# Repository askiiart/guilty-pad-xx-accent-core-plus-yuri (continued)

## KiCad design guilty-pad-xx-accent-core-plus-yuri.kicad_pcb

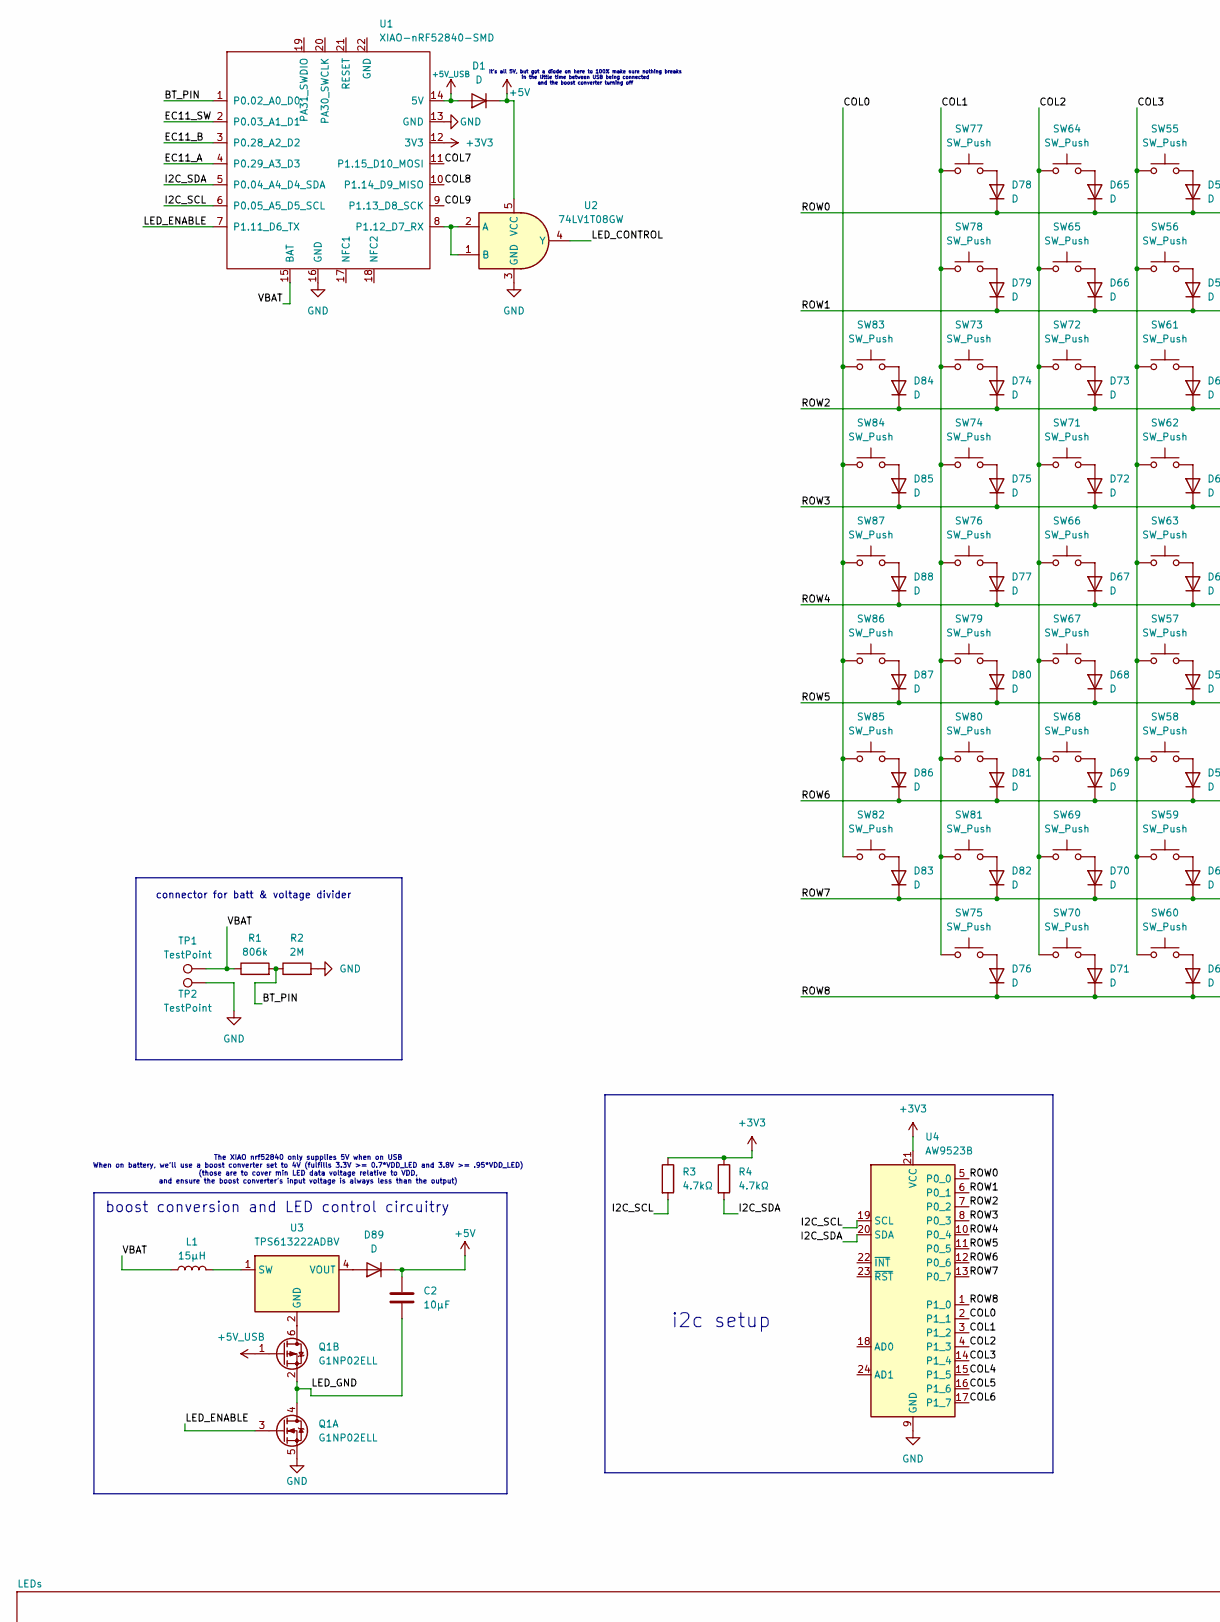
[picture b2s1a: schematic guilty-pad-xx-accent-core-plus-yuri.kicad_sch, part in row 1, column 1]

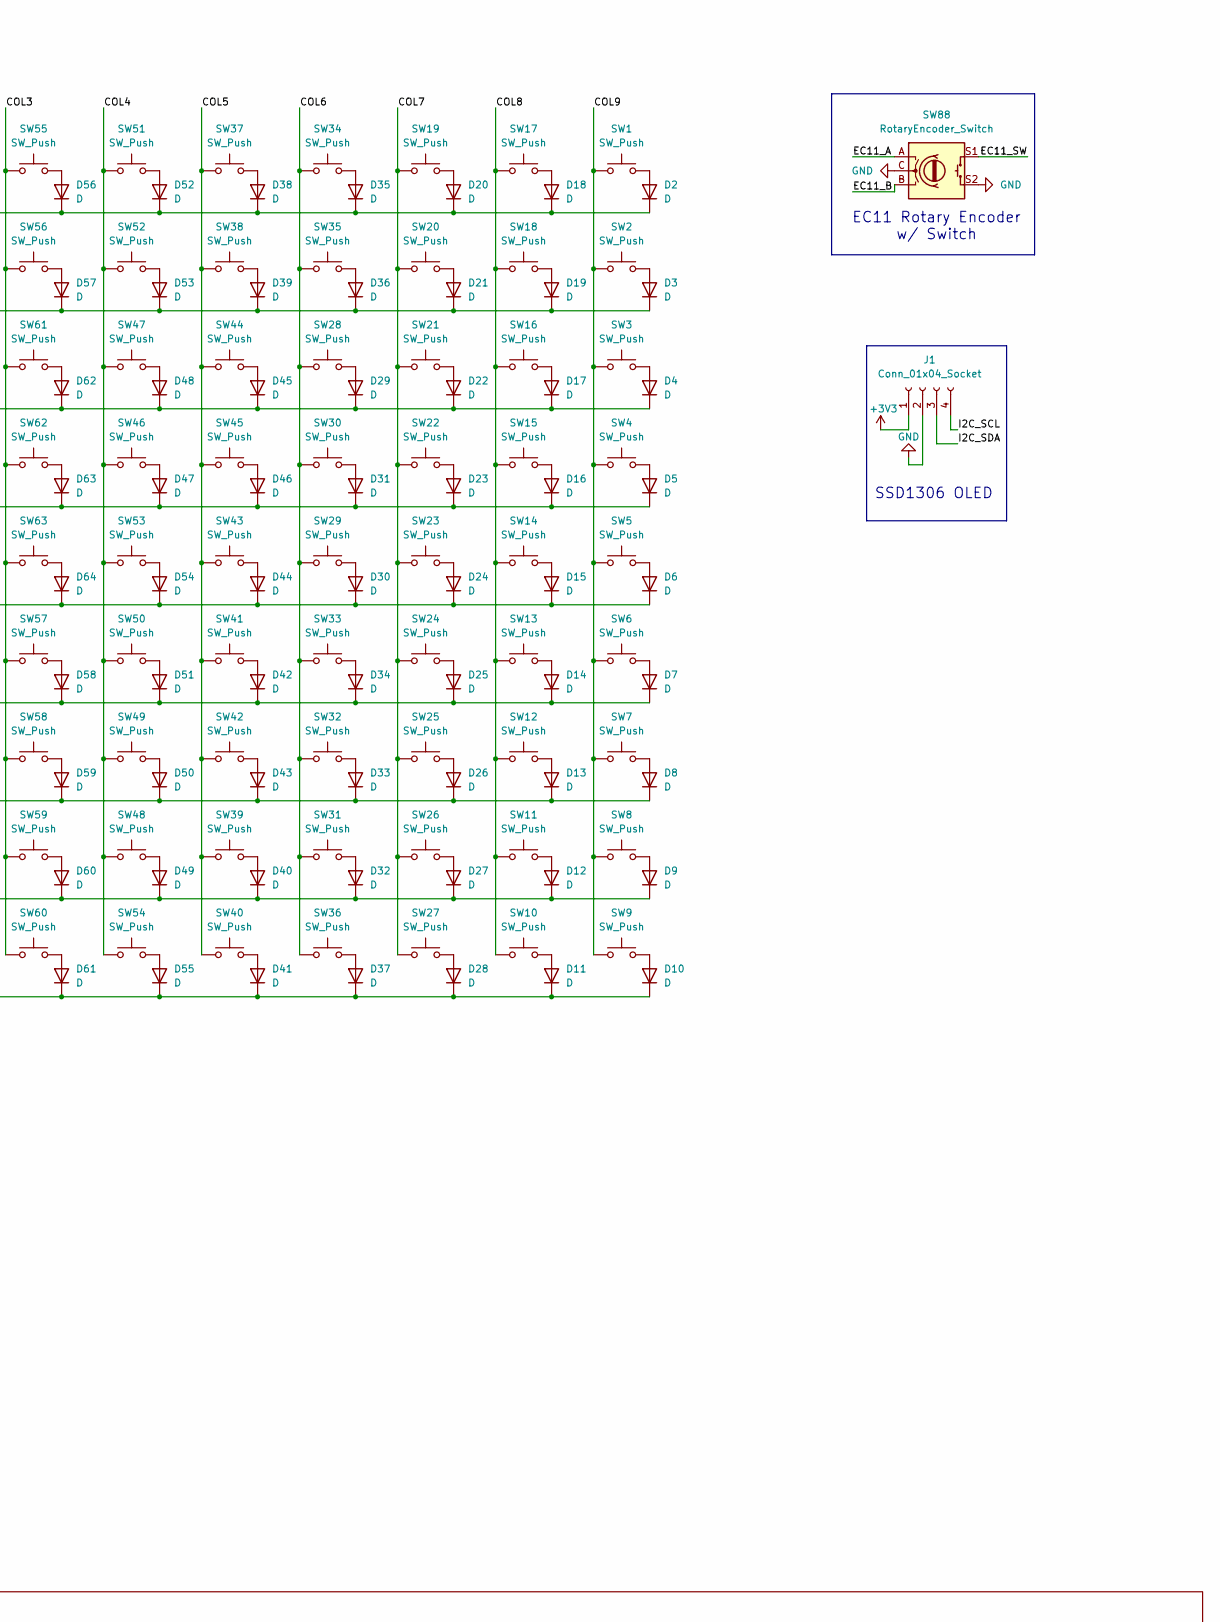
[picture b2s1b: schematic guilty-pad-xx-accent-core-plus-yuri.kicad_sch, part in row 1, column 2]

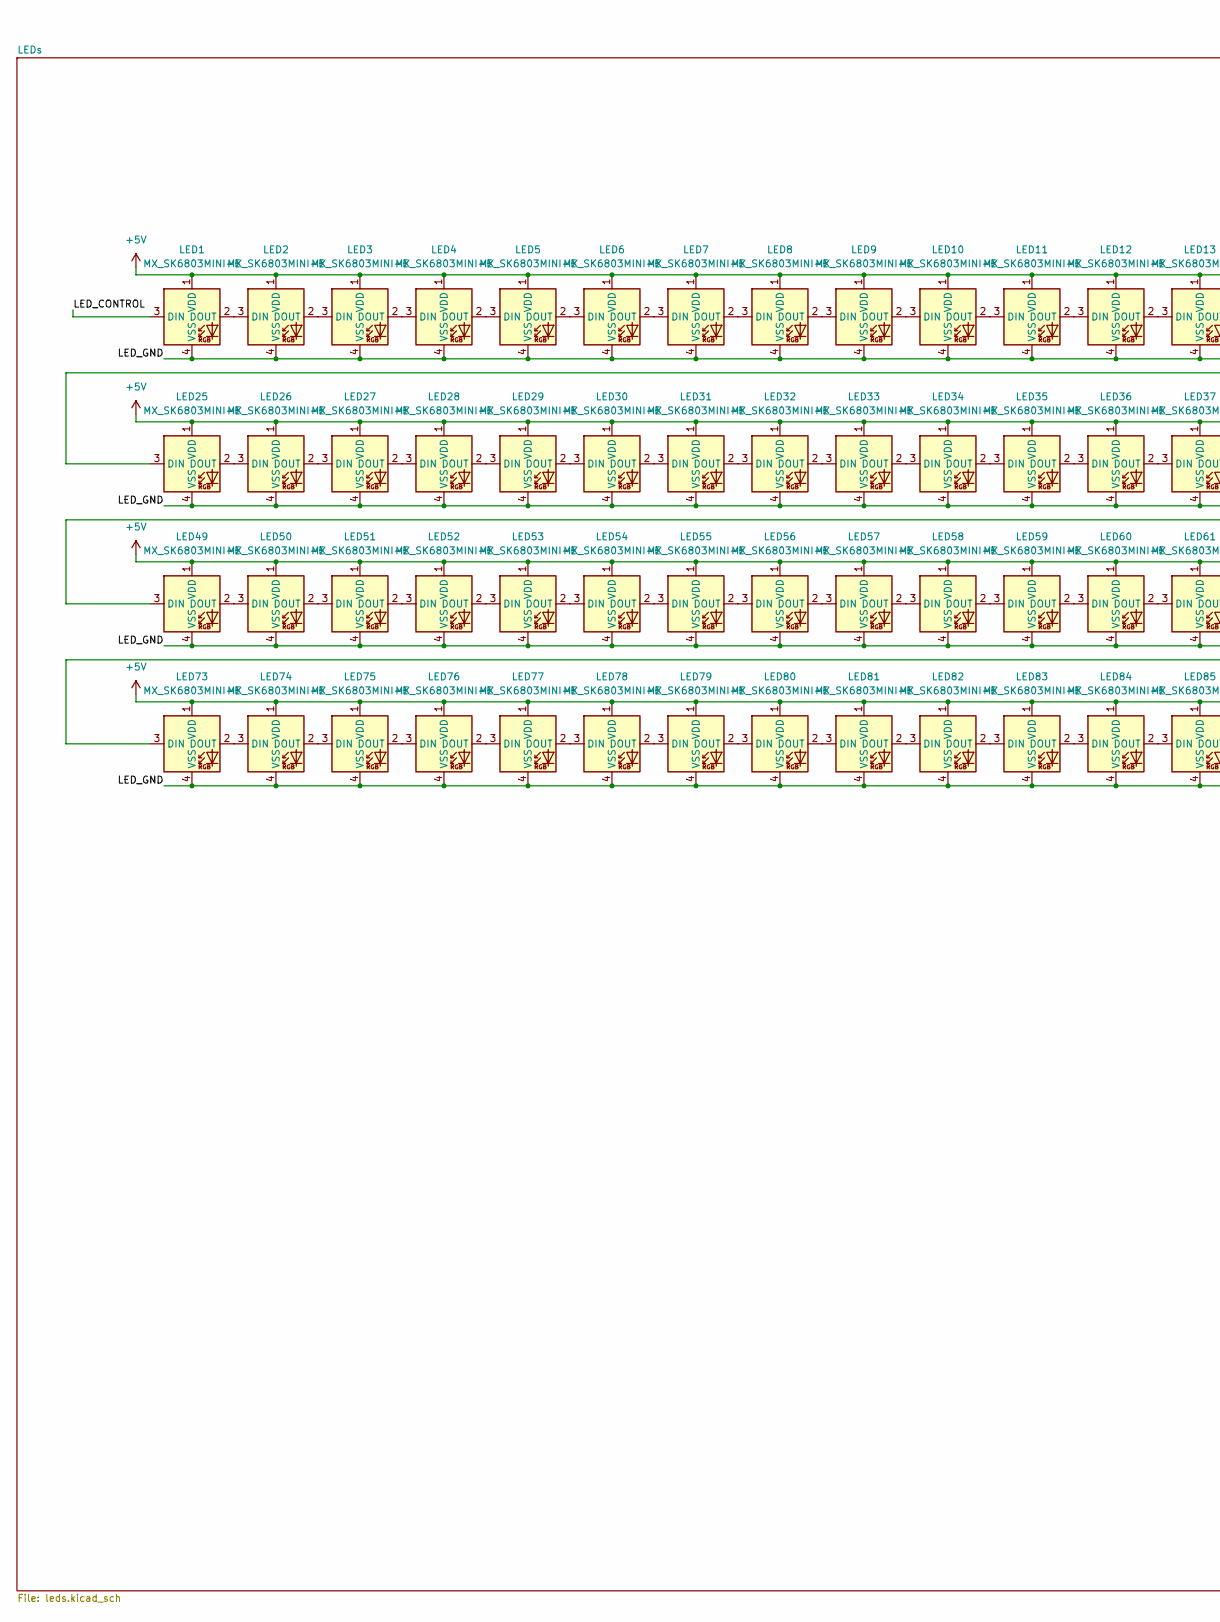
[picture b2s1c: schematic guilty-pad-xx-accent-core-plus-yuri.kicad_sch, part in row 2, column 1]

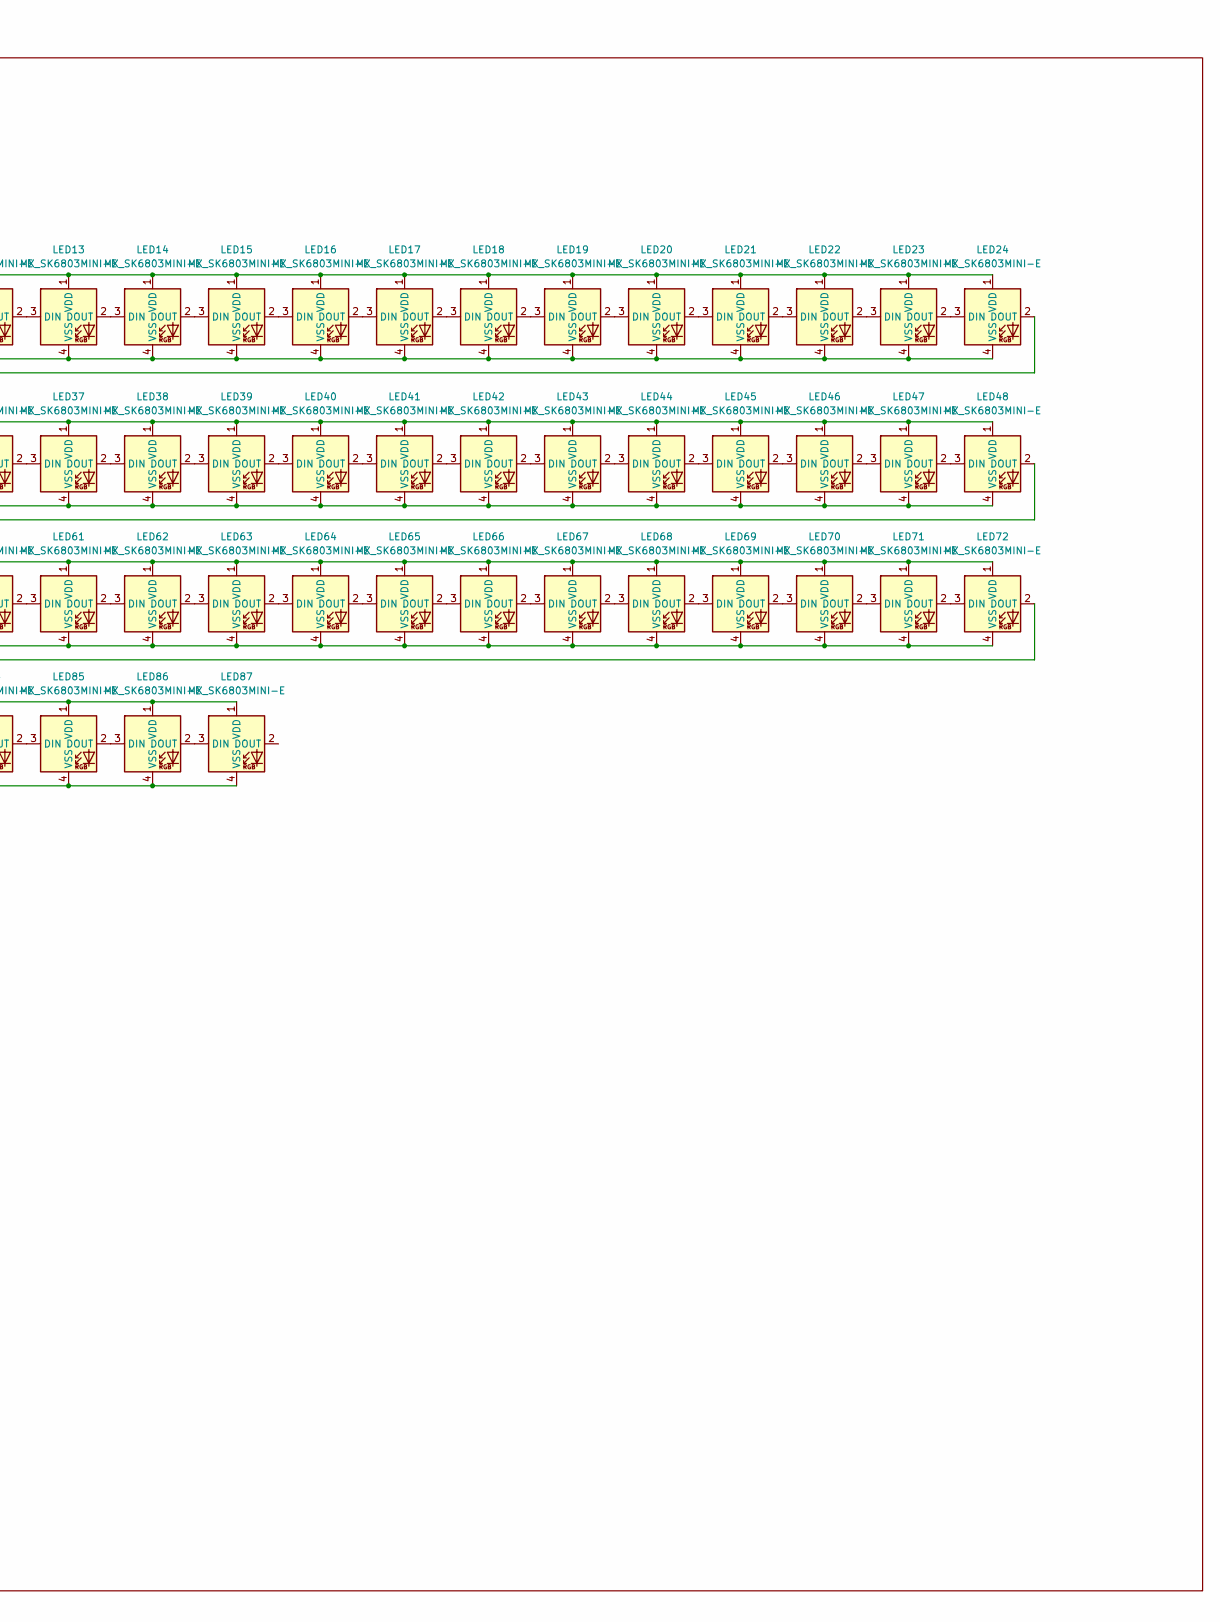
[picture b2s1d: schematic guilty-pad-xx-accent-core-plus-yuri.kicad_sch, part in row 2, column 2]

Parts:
C2: 10μF; C_0603_1608Metric_Pad1.08x0.95mm_HandSolder
D1, D2, D3, D4, D5, D6, D7, D8, D9, D10, D11, D12, D13, D14, D15, D16, D17, D18, D19, D20, D21, D22, D23, D24, D25, D26, D27, D28, D29, D30, D31, D32, D33, D34, D35, D36, D37, D38, D39, D40, D41, D42, D43, D44, D45, D46, D47, D48, D49, D50, D51, D52, D53, D54, D55, D56, D57, D58, D59, D60, D61, D62, D63, D64, D65, D66, D67, D68, D69, D70, D71, D72, D73, D74, D75, D76, D77, D78, D79, D80, D81, D82, D83, D84, D85, D86, D87, D88, D89: D; D_SMA_Handsoldering
J1: Conn_01x04_Socket; SSD1306-0.91-OLED-4pin-128x32
L1: 15μH; L_Wurth_WE-LQSH-4020
LED1, LED2, LED3, LED4, LED5, LED6, LED7, LED8, LED9, LED10, LED11, LED12, LED13, LED14, LED15, LED16, LED17, LED18, LED19, LED20, LED21, LED22, LED23, LED24, LED25, LED26, LED27, LED28, LED29, LED30, LED31, LED32, LED33, LED34, LED35, LED36, LED37, LED38, LED39, LED40, LED41, LED42, LED43, LED44, LED45, LED46, LED47, LED48, LED49, LED50, LED51, LED52, LED53, LED54, LED55, LED56, LED57, LED58, LED59, LED60, LED61, LED62, LED63, LED64, LED65, LED66, LED67, LED68, LED69, LED70, LED71, LED72, LED73, LED74, LED75, LED76, LED77, LED78, LED79, LED80, LED81, LED82, LED83, LED84, LED85, LED86, LED87: MX_SK6803MINI-E; LED_6028R
Q1: G1NP02ELL; TSOT-23-6_HandSoldering
R1: 806k; R_0402_1005Metric_Pad0.72x0.64mm_HandSolder
R2: 2M; R_0402_1005Metric_Pad0.72x0.64mm_HandSolder
R3, R4: 4.7kΩ; C_0402_1005Metric_Pad0.74x0.62mm_HandSolder
SW1, SW2, SW3, SW4, SW5, SW6, SW7, SW8, SW9, SW10, SW11, SW12, SW13, SW14, SW15, SW16, SW17, SW18, SW19, SW20, SW21, SW22, SW23, SW24, SW25, SW26, SW27, SW28, SW30, SW31, SW32, SW33, SW35, SW36, SW37, SW38, SW39, SW40, SW41, SW42, SW43, SW44, SW45, SW46, SW48, SW49, SW50, SW52, SW53, SW54, SW55, SW56, SW57, SW58, SW59, SW60, SW61, SW62, SW65, SW66, SW67, SW68, SW69, SW70, SW71, SW72, SW73, SW74, SW76, SW85, SW86, SW87: SW_Push; SW_Cherry_MX_1.00u_PCB
SW29: SW_Push; SW_Cherry_MX_2.00u_PCB
SW34, SW47: SW_Push; SW_Cherry_MX_1.50u_PCB
SW51: SW_Push; SW_Cherry_MX_1.75u_PCB
SW63, SW64: SW_Push; SW_Cherry_MX_2.25u_PCB
SW75: SW_Push; SW_Cherry_MX_2.75u_PCB
SW77, SW78, SW79, SW81, SW82, SW83, SW84: SW_Push; SW_Cherry_MX_1.25u_PCB
SW80: SW_Push; SW_Cherry_MX_6.25u_PCB
SW88: RotaryEncoder_Switch; RotaryEncoder_Alps_EC11E-Switch_Vertical_H20mm
TP1, TP2: TestPoint; TestPoint_Pad_2.0x2.0mm
U1: XIAO-nRF52840-SMD
U2: 74LV1T08GW; SOT-353_SC-70-5
U3: TPS613222ADBV; SOT-23-5
U4: AW9523B; QFN-24-1EP_4x4mm_P0.5mm_EP2.7x2.7mm

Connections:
+3V3: J1.1, R3.1, R4.1, U1.12 (3V3), U4.21 (VCC)
+5V: C2.2, D1.1 (K), D89.1 (K), LED1.1 (VDD), LED2.1 (VDD), LED3.1 (VDD), LED4.1 (VDD), LED5.1 (VDD), LED6.1 (VDD), LED7.1 (VDD), LED8.1 (VDD), LED9.1 (VDD), LED10.1 (VDD), LED11.1 (VDD), LED12.1 (VDD), LED13.1 (VDD), LED14.1 (VDD), LED15.1 (VDD), LED16.1 (VDD), LED17.1 (VDD), LED18.1 (VDD), LED19.1 (VDD), LED20.1 (VDD), LED21.1 (VDD), LED22.1 (VDD), LED23.1 (VDD), LED24.1 (VDD), LED25.1 (VDD), LED26.1 (VDD), LED27.1 (VDD), LED28.1 (VDD), LED29.1 (VDD), LED30.1 (VDD), LED31.1 (VDD), LED32.1 (VDD), LED33.1 (VDD), LED34.1 (VDD), LED35.1 (VDD), LED36.1 (VDD), LED37.1 (VDD), LED38.1 (VDD), LED39.1 (VDD), LED40.1 (VDD), LED41.1 (VDD), LED42.1 (VDD), LED43.1 (VDD), LED44.1 (VDD), LED45.1 (VDD), LED46.1 (VDD), LED47.1 (VDD), LED48.1 (VDD), LED49.1 (VDD), LED50.1 (VDD), LED51.1 (VDD), LED52.1 (VDD), LED53.1 (VDD), LED54.1 (VDD), LED55.1 (VDD), LED56.1 (VDD), LED57.1 (VDD), LED58.1 (VDD), LED59.1 (VDD), LED60.1 (VDD), LED61.1 (VDD), LED62.1 (VDD), LED63.1 (VDD), LED64.1 (VDD), LED65.1 (VDD), LED66.1 (VDD), LED67.1 (VDD), LED68.1 (VDD), LED69.1 (VDD), LED70.1 (VDD), LED71.1 (VDD), LED72.1 (VDD), LED73.1 (VDD), LED74.1 (VDD), LED75.1 (VDD), LED76.1 (VDD), LED77.1 (VDD), LED78.1 (VDD), LED79.1 (VDD), LED80.1 (VDD), LED81.1 (VDD), LED82.1 (VDD), LED83.1 (VDD), LED84.1 (VDD), LED85.1 (VDD), LED86.1 (VDD), LED87.1 (VDD), U2.5 (VCC)
+5V_USB: D1.2 (A), Q1.1 (G), U1.14 (5V)
/BT_PIN: R1.2, R2.1, U1.1 (P0.02_A0_D0)
/COL0: SW82.1, SW83.1, SW84.1, SW85.1, SW86.1, SW87.1, U4.2 (P1_1)
/COL1: SW73.1, SW74.1, SW75.1, SW76.1, SW77.1, SW78.1, SW79.1, SW80.1, SW81.1, U4.3 (P1_2)
/COL2: SW64.1, SW65.1, SW66.1, SW67.1, SW68.1, SW69.1, SW70.1, SW71.1, SW72.1, U4.4 (P1_3)
/COL3: SW55.1, SW56.1, SW57.1, SW58.1, SW59.1, SW60.1, SW61.1, SW62.1, SW63.1, U4.14 (P1_4)
/COL4: SW46.1, SW47.1, SW48.1, SW49.1, SW50.1, SW51.1, SW52.1, SW53.1, SW54.1, U4.15 (P1_5)
/COL5: SW37.1, SW38.1, SW39.1, SW40.1, SW41.1, SW42.1, SW43.1, SW44.1, SW45.1, U4.16 (P1_6)
/COL6: SW28.1, SW29.1, SW30.1, SW31.1, SW32.1, SW33.1, SW34.1, SW35.1, SW36.1, U4.17 (P1_7)
/COL7: SW19.1, SW20.1, SW21.1, SW22.1, SW23.1, SW24.1, SW25.1, SW26.1, SW27.1, U1.11 (P1.15_D10_MOSI)
/COL8: SW10.1, SW11.1, SW12.1, SW13.1, SW14.1, SW15.1, SW16.1, SW17.1, SW18.1, U1.10 (P1.14_D9_MISO)
/COL9: SW1.1, SW2.1, SW3.1, SW4.1, SW5.1, SW6.1, SW7.1, SW8.1, SW9.1, U1.9 (P1.13_D8_SCK)
/EC11_A: SW88.A, U1.4 (P0.29_A3_D3)
/EC11_B: SW88.B, U1.3 (P0.28_A2_D2)
/EC11_SW: SW88.S1, U1.2 (P0.03_A1_D1)
/I2C_SCL: J1.4, R3.2, U1.6 (P0.05_A5_D5_SCL), U4.19 (SCL)
/I2C_SDA: J1.3, R4.2, U1.5 (P0.04_A4_D4_SDA), U4.20 (SDA)
/LED_CONTROL: LED1.3 (DIN), U2.4 (Y)
/LED_ENABLE: Q1.3 (G), U1.7 (P1.11_D6_TX)
/LED_GND: C2.1, LED1.4 (VSS), LED2.4 (VSS), LED3.4 (VSS), LED4.4 (VSS), LED5.4 (VSS), LED6.4 (VSS), LED7.4 (VSS), LED8.4 (VSS), LED9.4 (VSS), LED10.4 (VSS), LED11.4 (VSS), LED12.4 (VSS), LED13.4 (VSS), LED14.4 (VSS), LED15.4 (VSS), LED16.4 (VSS), LED17.4 (VSS), LED18.4 (VSS), LED19.4 (VSS), LED20.4 (VSS), LED21.4 (VSS), LED22.4 (VSS), LED23.4 (VSS), LED24.4 (VSS), LED25.4 (VSS), LED26.4 (VSS), LED27.4 (VSS), LED28.4 (VSS), LED29.4 (VSS), LED30.4 (VSS), LED31.4 (VSS), LED32.4 (VSS), LED33.4 (VSS), LED34.4 (VSS), LED35.4 (VSS), LED36.4 (VSS), LED37.4 (VSS), LED38.4 (VSS), LED39.4 (VSS), LED40.4 (VSS), LED41.4 (VSS), LED42.4 (VSS), LED43.4 (VSS), LED44.4 (VSS), LED45.4 (VSS), LED46.4 (VSS), LED47.4 (VSS), LED48.4 (VSS), LED49.4 (VSS), LED50.4 (VSS), LED51.4 (VSS), LED52.4 (VSS), LED53.4 (VSS), LED54.4 (VSS), LED55.4 (VSS), LED56.4 (VSS), LED57.4 (VSS), LED58.4 (VSS), LED59.4 (VSS), LED60.4 (VSS), LED61.4 (VSS), LED62.4 (VSS), LED63.4 (VSS), LED64.4 (VSS), LED65.4 (VSS), LED66.4 (VSS), LED67.4 (VSS), LED68.4 (VSS), LED69.4 (VSS), LED70.4 (VSS), LED71.4 (VSS), LED72.4 (VSS), LED73.4 (VSS), LED74.4 (VSS), LED75.4 (VSS), LED76.4 (VSS), LED77.4 (VSS), LED78.4 (VSS), LED79.4 (VSS), LED80.4 (VSS), LED81.4 (VSS), LED82.4 (VSS), LED83.4 (VSS), LED84.4 (VSS), LED85.4 (VSS), LED86.4 (VSS), LED87.4 (VSS), Q1.2 (S), Q1.4 (D)
/ROW0: D2.1 (K), D18.1 (K), D20.1 (K), D35.1 (K), D38.1 (K), D52.1 (K), D56.1 (K), D65.1 (K), D78.1 (K), U4.5 (P0_0)
/ROW1: D3.1 (K), D19.1 (K), D21.1 (K), D36.1 (K), D39.1 (K), D53.1 (K), D57.1 (K), D66.1 (K), D79.1 (K), U4.6 (P0_1)
/ROW2: D4.1 (K), D17.1 (K), D22.1 (K), D29.1 (K), D45.1 (K), D48.1 (K), D62.1 (K), D73.1 (K), D74.1 (K), D84.1 (K), U4.7 (P0_2)
/ROW3: D5.1 (K), D16.1 (K), D23.1 (K), D31.1 (K), D46.1 (K), D47.1 (K), D63.1 (K), D72.1 (K), D75.1 (K), D85.1 (K), U4.8 (P0_3)
/ROW4: D6.1 (K), D15.1 (K), D24.1 (K), D30.1 (K), D44.1 (K), D54.1 (K), D64.1 (K), D67.1 (K), D77.1 (K), D88.1 (K), U4.10 (P0_4)
/ROW5: D7.1 (K), D14.1 (K), D25.1 (K), D34.1 (K), D42.1 (K), D51.1 (K), D58.1 (K), D68.1 (K), D80.1 (K), D87.1 (K), U4.11 (P0_5)
/ROW6: D8.1 (K), D13.1 (K), D26.1 (K), D33.1 (K), D43.1 (K), D50.1 (K), D59.1 (K), D69.1 (K), D81.1 (K), D86.1 (K), U4.12 (P0_6)
/ROW7: D9.1 (K), D12.1 (K), D27.1 (K), D32.1 (K), D40.1 (K), D49.1 (K), D60.1 (K), D70.1 (K), D82.1 (K), D83.1 (K), U4.13 (P0_7)
/ROW8: D10.1 (K), D11.1 (K), D28.1 (K), D37.1 (K), D41.1 (K), D55.1 (K), D61.1 (K), D71.1 (K), D76.1 (K), U4.1 (P1_0)
/VBAT: L1.1, R1.1, TP1.1, U1.15 (BAT)
GND: J1.2, Q1.5 (S), R2.2, SW88.C, SW88.S2, TP2.1, U1.13 (GND), U1.16 (GND), U2.3 (GND), U4.9 (GND), U4.25 (GND)
unnamed: D2.2 (A), SW1.2
unnamed: D3.2 (A), SW2.2
unnamed: D4.2 (A), SW3.2
unnamed: D5.2 (A), SW4.2
unnamed: D6.2 (A), SW5.2
unnamed: D7.2 (A), SW6.2
unnamed: D8.2 (A), SW7.2
unnamed: D9.2 (A), SW8.2
unnamed: D10.2 (A), SW9.2
unnamed: D11.2 (A), SW10.2
unnamed: D12.2 (A), SW11.2
unnamed: D13.2 (A), SW12.2
unnamed: D14.2 (A), SW13.2
unnamed: D15.2 (A), SW14.2
unnamed: D16.2 (A), SW15.2
unnamed: D17.2 (A), SW16.2
unnamed: D18.2 (A), SW17.2
unnamed: D19.2 (A), SW18.2
unnamed: D20.2 (A), SW19.2
unnamed: D21.2 (A), SW20.2
unnamed: D22.2 (A), SW21.2
unnamed: D23.2 (A), SW22.2
unnamed: D24.2 (A), SW23.2
unnamed: D25.2 (A), SW24.2
unnamed: D26.2 (A), SW25.2
unnamed: D27.2 (A), SW26.2
unnamed: D28.2 (A), SW27.2
unnamed: D29.2 (A), SW28.2
unnamed: D30.2 (A), SW29.2
unnamed: D31.2 (A), SW30.2
unnamed: D32.2 (A), SW31.2
unnamed: D33.2 (A), SW32.2
unnamed: D34.2 (A), SW33.2
unnamed: D35.2 (A), SW34.2
unnamed: D36.2 (A), SW35.2
unnamed: D37.2 (A), SW36.2
unnamed: D38.2 (A), SW37.2
unnamed: D39.2 (A), SW38.2
unnamed: D40.2 (A), SW39.2
unnamed: D41.2 (A), SW40.2
unnamed: D42.2 (A), SW41.2
unnamed: D43.2 (A), SW42.2
unnamed: D44.2 (A), SW43.2
unnamed: D45.2 (A), SW44.2
unnamed: D46.2 (A), SW45.2
unnamed: D47.2 (A), SW46.2
unnamed: D48.2 (A), SW47.2
unnamed: D49.2 (A), SW48.2
unnamed: D50.2 (A), SW49.2
unnamed: D51.2 (A), SW50.2
unnamed: D52.2 (A), SW51.2
unnamed: D53.2 (A), SW52.2
unnamed: D54.2 (A), SW53.2
unnamed: D55.2 (A), SW54.2
unnamed: D56.2 (A), SW55.2
unnamed: D57.2 (A), SW56.2
unnamed: D58.2 (A), SW57.2
unnamed: D59.2 (A), SW58.2
unnamed: D60.2 (A), SW59.2
unnamed: D61.2 (A), SW60.2
unnamed: D62.2 (A), SW61.2
unnamed: D63.2 (A), SW62.2
unnamed: D64.2 (A), SW63.2
unnamed: D65.2 (A), SW64.2
unnamed: D66.2 (A), SW65.2
unnamed: D67.2 (A), SW66.2
unnamed: D68.2 (A), SW67.2
unnamed: D69.2 (A), SW68.2
unnamed: D70.2 (A), SW69.2
unnamed: D71.2 (A), SW70.2
unnamed: D72.2 (A), SW71.2
unnamed: D73.2 (A), SW72.2
unnamed: D74.2 (A), SW73.2
unnamed: D75.2 (A), SW74.2
unnamed: D76.2 (A), SW75.2
unnamed: D77.2 (A), SW76.2
unnamed: D78.2 (A), SW77.2
unnamed: D79.2 (A), SW78.2
unnamed: D80.2 (A), SW79.2
unnamed: D81.2 (A), SW80.2
unnamed: D82.2 (A), SW81.2
unnamed: D83.2 (A), SW82.2
unnamed: D84.2 (A), SW83.2
unnamed: D85.2 (A), SW84.2
unnamed: D86.2 (A), SW85.2
unnamed: D87.2 (A), SW86.2
unnamed: D88.2 (A), SW87.2
unnamed: D89.2 (A), U3.4 (VOUT)
unnamed: LED1.2 (DOUT), LED2.3 (DIN)
unnamed: LED2.2 (DOUT), LED3.3 (DIN)
unnamed: LED3.2 (DOUT), LED4.3 (DIN)
unnamed: LED4.2 (DOUT), LED5.3 (DIN)
unnamed: LED5.2 (DOUT), LED6.3 (DIN)
unnamed: LED6.2 (DOUT), LED7.3 (DIN)
unnamed: LED7.2 (DOUT), LED8.3 (DIN)
unnamed: LED8.2 (DOUT), LED9.3 (DIN)
unnamed: LED9.2 (DOUT), LED10.3 (DIN)
unnamed: LED10.2 (DOUT), LED11.3 (DIN)
unnamed: LED11.2 (DOUT), LED12.3 (DIN)
unnamed: LED12.2 (DOUT), LED13.3 (DIN)
unnamed: LED13.2 (DOUT), LED14.3 (DIN)
unnamed: LED14.2 (DOUT), LED15.3 (DIN)
unnamed: LED15.2 (DOUT), LED16.3 (DIN)
unnamed: LED16.2 (DOUT), LED17.3 (DIN)
unnamed: LED17.2 (DOUT), LED18.3 (DIN)
unnamed: LED18.2 (DOUT), LED19.3 (DIN)
unnamed: LED19.2 (DOUT), LED20.3 (DIN)
unnamed: LED20.2 (DOUT), LED21.3 (DIN)
unnamed: LED21.2 (DOUT), LED22.3 (DIN)
unnamed: LED22.2 (DOUT), LED23.3 (DIN)
unnamed: LED23.2 (DOUT), LED24.3 (DIN)
unnamed: LED24.2 (DOUT), LED25.3 (DIN)
unnamed: LED25.2 (DOUT), LED26.3 (DIN)
unnamed: LED26.2 (DOUT), LED27.3 (DIN)
unnamed: LED27.2 (DOUT), LED28.3 (DIN)
unnamed: LED28.2 (DOUT), LED29.3 (DIN)
unnamed: LED29.2 (DOUT), LED30.3 (DIN)
unnamed: LED30.2 (DOUT), LED31.3 (DIN)
unnamed: LED31.2 (DOUT), LED32.3 (DIN)
unnamed: LED32.2 (DOUT), LED33.3 (DIN)
unnamed: LED33.2 (DOUT), LED34.3 (DIN)
unnamed: LED34.2 (DOUT), LED35.3 (DIN)
unnamed: LED35.2 (DOUT), LED36.3 (DIN)
unnamed: LED36.2 (DOUT), LED37.3 (DIN)
unnamed: LED37.2 (DOUT), LED38.3 (DIN)
unnamed: LED38.2 (DOUT), LED39.3 (DIN)
unnamed: LED39.2 (DOUT), LED40.3 (DIN)
unnamed: LED40.2 (DOUT), LED41.3 (DIN)
unnamed: LED41.2 (DOUT), LED42.3 (DIN)
unnamed: LED42.2 (DOUT), LED43.3 (DIN)
unnamed: LED43.2 (DOUT), LED44.3 (DIN)
unnamed: LED44.2 (DOUT), LED45.3 (DIN)
unnamed: LED45.2 (DOUT), LED46.3 (DIN)
unnamed: LED46.2 (DOUT), LED47.3 (DIN)
unnamed: LED47.2 (DOUT), LED48.3 (DIN)
unnamed: LED48.2 (DOUT), LED49.3 (DIN)
unnamed: LED49.2 (DOUT), LED50.3 (DIN)
unnamed: LED50.2 (DOUT), LED51.3 (DIN)
unnamed: LED51.2 (DOUT), LED52.3 (DIN)
unnamed: LED52.2 (DOUT), LED53.3 (DIN)
unnamed: LED53.2 (DOUT), LED54.3 (DIN)
unnamed: LED54.2 (DOUT), LED55.3 (DIN)
unnamed: LED55.2 (DOUT), LED56.3 (DIN)
unnamed: LED56.2 (DOUT), LED57.3 (DIN)
unnamed: LED57.2 (DOUT), LED58.3 (DIN)
unnamed: LED58.2 (DOUT), LED59.3 (DIN)
unnamed: LED59.2 (DOUT), LED60.3 (DIN)
unnamed: LED60.2 (DOUT), LED61.3 (DIN)
unnamed: LED61.2 (DOUT), LED62.3 (DIN)
unnamed: LED62.2 (DOUT), LED63.3 (DIN)
unnamed: LED63.2 (DOUT), LED64.3 (DIN)
unnamed: LED64.2 (DOUT), LED65.3 (DIN)
unnamed: LED65.2 (DOUT), LED66.3 (DIN)
unnamed: LED66.2 (DOUT), LED67.3 (DIN)
unnamed: LED67.2 (DOUT), LED68.3 (DIN)
unnamed: LED68.2 (DOUT), LED69.3 (DIN)
unnamed: LED69.2 (DOUT), LED70.3 (DIN)
unnamed: LED70.2 (DOUT), LED71.3 (DIN)
unnamed: LED71.2 (DOUT), LED72.3 (DIN)
unnamed: LED72.2 (DOUT), LED73.3 (DIN)
unnamed: LED73.2 (DOUT), LED74.3 (DIN)
unnamed: LED74.2 (DOUT), LED75.3 (DIN)
unnamed: LED75.2 (DOUT), LED76.3 (DIN)
unnamed: LED76.2 (DOUT), LED77.3 (DIN)
unnamed: LED77.2 (DOUT), LED78.3 (DIN)
unnamed: LED78.2 (DOUT), LED79.3 (DIN)
unnamed: LED79.2 (DOUT), LED80.3 (DIN)
unnamed: LED80.2 (DOUT), LED81.3 (DIN)
unnamed: LED81.2 (DOUT), LED82.3 (DIN)
unnamed: LED82.2 (DOUT), LED83.3 (DIN)
unnamed: LED83.2 (DOUT), LED84.3 (DIN)
unnamed: LED84.2 (DOUT), LED85.3 (DIN)
unnamed: LED85.2 (DOUT), LED86.3 (DIN)
unnamed: LED86.2 (DOUT), LED87.3 (DIN)
unnamed: Q1.6 (D), U3.2 (GND)
unnamed: U1.8 (P1.12_D7_RX), U2.1 (B), U2.2 (A)
unnamed: L1.2, U3.1 (SW)

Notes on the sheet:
It's all 5V, but got a diode on here to 100% make sure nothing breaks in the little time between USB being connected and the boost converter turning off
connector for batt & voltage divider
EC11 Rotary Encoder w/ Switch
The XIAO nrf52840 only supplies 5V when on USB When on battery, we'll use a boost converter set to 4V (fulfills 3.3V >= 0.7*VDD_LED and 3.8V >= .95*VDD_LED) (those are to cover min LED data voltage relative to VDD, and ensure the boost converter's input voltage is always less than the output)
i2c setup
boost conversion and LED control circuitry
SSD1306 OLED

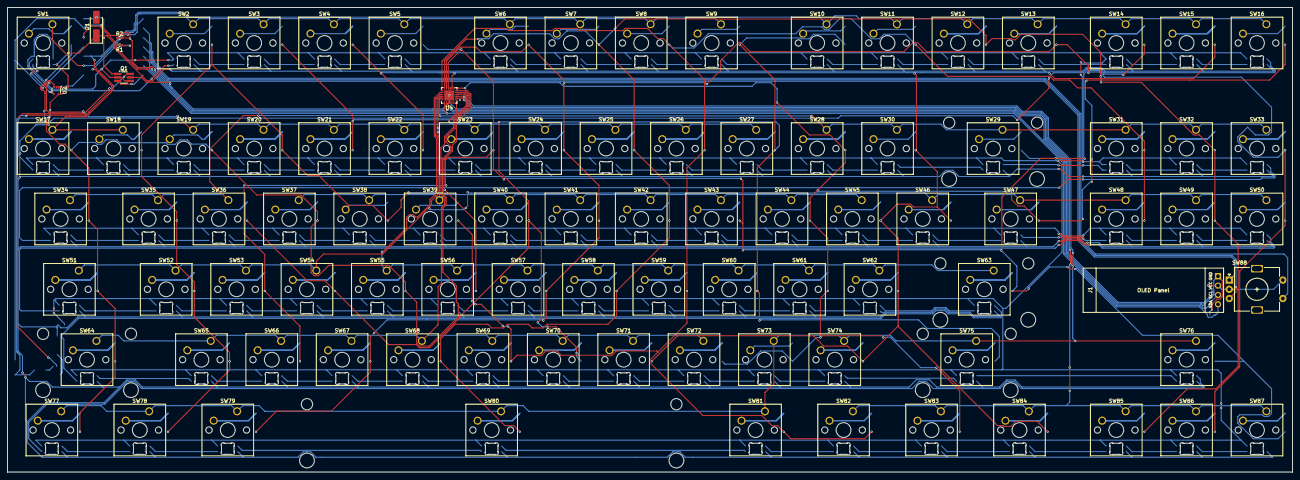
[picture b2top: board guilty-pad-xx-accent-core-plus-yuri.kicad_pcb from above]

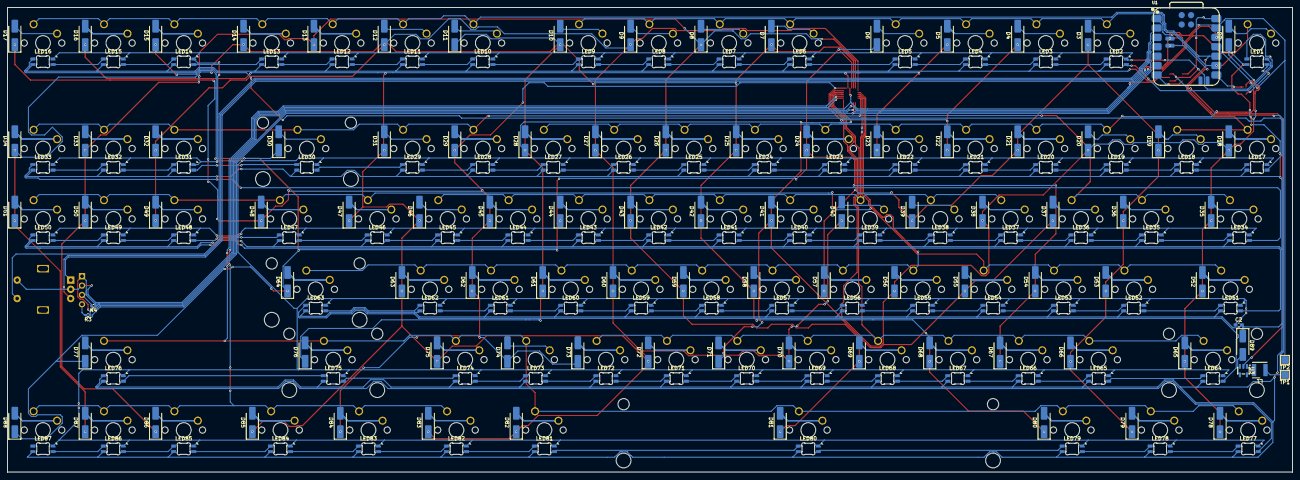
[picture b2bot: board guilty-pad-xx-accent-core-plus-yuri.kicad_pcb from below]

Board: 2 copper layers, 347.9 x 125.8 mm, 278 parts (183 on the bottom side), 210 nets.

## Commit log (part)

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2025-11-30 schematic's just about done aside from rotary encoder
2025-12-03 schematic and pcb are done, images for those are added
2025-12-04 update readme and add bom
2025-12-05 update README/BOM, use 4.7k resistors for i2c pullup
2025-12-06 fix BOM
2025-12-06 no real schematic changes, just fix an old comment
2025-12-06 add firmware
2025-12-06 add case and update readme with it
2025-12-06 move kicad stuff to PCB folder
2025-12-07 add case in step format
2025-12-07 move 3d-models to pcb dir
2025-12-08 fix library path - no real changes
2025-12-08 add gerber.zip
2025-12-20 clean up tracks/vias
2026-01-09 update with hotswap and stuff idek
